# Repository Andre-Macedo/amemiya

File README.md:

# Sistema de Metrologia Lean Tech (Amemiya)

Plataforma integrada de metrologia industrial, gestão de conformidade (ISO/IEC 17025, ILAC-G8, OIML D10, FDA 21 CFR Part 11) e monitoramento contínuo com IoT e inteligência artificial (XGBoost).

---

## 1. Visão Geral da Arquitetura

```mermaid
graph TD
    subgraph Frontend & Clients
        UI["Next.js 16 Frontend (metrology-sass-front)"]
        Admin["Filament 4 Admin Panel (:8000)"]
        Sensors["Sensores Industriais / ESP32 Nodes"]
    end

    subgraph Backend Core (Amemiya)
        Nginx["Nginx (:8000)"]
        App["amemiya-app (PHP 8.3 FPM)"]
        Reverb["Laravel Reverb (:8080 WebSockets)"]
        Worker["Queue Worker (Laravel Queues)"]
        Bridge["MQTT Bridge (iot:mqtt-bridge)"]
    end

    subgraph Data & Messaging
        DB[("MySQL 8.0 (:3307)")]
        Redis[("Redis 7.x (:6379)")]
        MQTT["Mosquitto Broker (:1883)"]
    end

    subgraph Machine Learning
        ML["ML Service (FastAPI / XGBoost :8000)"]
    end

    Sensors -->|MQTT QoS 1| MQTT
    MQTT -->|iot:mqtt-bridge| Bridge
    Bridge --> Redis
    Bridge --> App

    UI -->|REST API| Nginx
    UI -->|WebSockets| Reverb
    Admin --> Nginx
    Nginx --> App

    App --> DB
    App --> Redis
    App --> ML
    Worker --> Redis
    Worker --> DB
    App -->|Broadcast| Reverb
```

---

## 2. Módulos da Aplicação

O sistema é construído sobre uma **arquitetura modular** (`nwidart/laravel-modules`):

- **[`Modules/Metrology/`](Modules/Metrology)**: Motor metrológico completo. Gestão de calibrações, instrumentos, padrões de referência RBC, cálculo de incerteza de medição conforme GUM, bandas de guarda (ILAC-G8), otimização de intervalos (OIML D10), cartas de controle de Shewhart (ILAC-G24), laudos forenses com assinatura digital SHA-256 e trilha encadeada de auditoria imutável (FDA 21 CFR Part 11).
- **[`Modules/IoT/`](Modules/IoT)**: Ingestão de telemetria industrial de vibração e temperatura em tempo real via Mosquitto MQTT, classificação de severidade conforme ISO 20816-3 e integração com modelo preditivo de anomalias.
- **[`Modules/System/`](Modules/System)**: Multi-tenancy central, perfis e matriz de permissões via Filament Shield, auditoria Spatie Activitylog e usuários.
- **[`hardware/`](hardware)**: Projetos completos de eletrônica (KiCad) e mecânica (Autodesk Fusion 360 / STEP) para os nós sensores, gateway LoRa e bancada industrial com proteção NR-12.

---

## 3. Guia Rápido de Instalação (Docker)

### Pré-requisitos
- [Docker Desktop](https://www.docker.com/products/docker-desktop/) (com suporte a Docker Compose v2)
- [Git](https://git-scm.com/)

### Passo a Passo

1. **Clonar o repositório:**
   ```bash
   git clone git@github.com:Andre-Macedo/amemiya.git
   cd amemiya
   ```

2. **Configurar variáveis de ambiente:**
   ```bash
   cp .env.example .env
   ```

3. **Subir os containers:**
   ```bash
   docker compose up -d --build
   ```

4. **Instalar dependências e preparar a aplicação:**
   ```bash
   docker compose exec app composer install
   docker compose exec app php artisan key:generate
   docker compose exec app php artisan migrate
   docker compose exec app php artisan module:migrate Metrology
   docker compose exec app php artisan module:migrate IoT
   docker compose exec app php artisan module:seed Metrology
   docker compose exec app php artisan storage:link
   ```

5. **Criar o usuário administrador do Filament:**
   ```bash
   docker compose exec app php artisan make:filament-user
   ```

---

## 4. Portas e Serviços Locais

| Serviço | Porta Local | Descrição |
| :--- | :--- | :--- |
| **Painel Filament / API** | [http://localhost:8000](http://localhost:8000) | Aplicação web principal |
| **Frontend Next.js** | [http://localhost:3000](http://localhost:3000) | Interface do cliente e monitor IoT |
| **phpMyAdmin** | [http://localhost:8080](http://localhost:8080) | Gerenciador web do MySQL (root/rootpass) |
| **MailHog (SMTP)** | [http://localhost:8025](http://localhost:8025) | Caixa de entrada para e-mails de teste |
| **Mosquitto MQTT** | `localhost:1883` | Broker de mensagens IoT |
| **Redis** | `localhost:6379` | Cache e filas de processamento |
| **MySQL 8.0** | `localhost:3307` | Banco de dados relacional |
| **Laravel Reverb** | `localhost:8080` | Servidor de WebSockets |

---

## 5. Scripts de Qualidade e Testes

Antes de submeter código, execute os scripts de verificação:

```bash
# Executar todos os testes automatizados (Pest)
docker compose exec app composer test

# Verificação de formatação de código (Laravel Pint)
docker compose exec app composer format:test

# Correção automática de formatação
docker compose exec app composer format

# Análise estática de tipos (PHPStan / Larastan)
docker compose exec app composer analyse

# Validação completa de qualidade (Pint + Larastan + Pest)
docker compose exec app composer quality
```

---

## 6. Fluxo de Contribuição e Branches

- **Branch principal de desenvolvimento:** **`develop`**
- **Branch de produção:** **`main`**
- **Todas as Pull Requests devem ter como destino a branch `develop`.**
- Consulte o guia completo em [`CONTRIBUTING.md`](CONTRIBUTING.md) para detalhes sobre Conventional Commits e padrões de arquitetura.

---

## 7. Índice de Documentação Técnica

- **Metrologia e Qualidade:**
  - [`Modules/Metrology/docs/BUSINESS_RULES.md`](Modules/Metrology/docs/BUSINESS_RULES.md) — Manual canônico de regras de negócio, normas ISO e cálculos.
  - [`docs/metrology/METROLOGY_MODULE_GUIDE.md`](docs/metrology/METROLOGY_MODULE_GUIDE.md) — Guia arquitetural completo, diagramas ER e conformidade normativa.
  - [`docs/metrology/USER_ACCEPTANCE_TESTS.md`](docs/metrology/USER_ACCEPTANCE_TESTS.md) — Roteiros de testes de aceitação de usuário (UAT).
- **IoT, Telemetria e MLOps:**
  - [`docs/iot/DECISOES_TECNICAS_E_REFERENCIAS_CIENTIFICAS.md`](docs/iot/DECISOES_TECNICAS_E_REFERENCIAS_CIENTIFICAS.md) — Fundamentação científica e amostragem de vibração.
  - [`docs/iot/REGRAS_DE_NEGOCIO_MLOPS_E_AMOSTRAGEM.md`](docs/iot/REGRAS_DE_NEGOCIO_MLOPS_E_AMOSTRAGEM.md) — Pipeline de machine learning e triagem de anomalias.
  - [`docs/iot/MQTT_SECURITY.md`](docs/iot/MQTT_SECURITY.md) — Diretrizes de segurança, isolamento e ACL do Mosquitto.
  - [`docs/iot/RELATORIO_PCBS.md`](docs/iot/RELATORIO_PCBS.md) — Especificações de eletrônica e esquemáticos.
- **Arquitetura Geral:**
  - [`docs/architecture/TENANCY_ARCHITECTURE.md`](docs/architecture/TENANCY_ARCHITECTURE.md) — Isolamento de dados multi-tenant.
  - [`docs/architecture/WEBSOCKETS_REVERB_GUIDE.md`](docs/architecture/WEBSOCKETS_REVERB_GUIDE.md) — Guia de integração Reverb WebSockets.
  - [`docs/architecture/IMPROVEMENT_PLAN.md`](docs/architecture/IMPROVEMENT_PLAN.md) — Roadmap de melhorias e evolução contínua.

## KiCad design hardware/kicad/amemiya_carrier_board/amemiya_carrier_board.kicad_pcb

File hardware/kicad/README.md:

# Amemiya IoT — Projetos de PCB KiCad (v2.0)

Este repositório contém os projetos de placas de circuito impresso (PCB) desenvolvidos para o sistema de manutenção preditiva e IoT industrial **Amemiya**.

---

## Estrutura dos Projetos KiCad

Os projetos foram modelados de forma **100% modular**, onde os módulos de sensores, microcontrolador e rádio são encaixados na PCB principal através de **soquetes de barra de pinos fêmea (headers 2.54 mm)**, permitindo substituição rápida de qualquer componente sem necessidade de solda direta nos chips.

```
hardware/kicad/
├── amemiya_probe_sensor/            # PCB 1: Sonda de Mancal Ultra-Compacta (25x25 mm)
│   ├── amemiya_probe_sensor.kicad_sch  # Esquemático elétrico KiCad
│   └── amemiya_probe_sensor.kicad_pcb  # Layout da placa PCB
├── amemiya_main_node/               # PCB 2: Nó de Borda Principal ESP32-S3 (70x50 mm)
│   ├── amemiya_main_node.kicad_sch     # Esquemático elétrico KiCad
│   └── amemiya_main_node.kicad_pcb     # Layout da placa PCB
├── amemiya_probe_tower/             # PCB 3: Sonda Cartucho Torre Cilíndrica (24x48 mm)
│   └── amemiya_probe_tower.kicad_pcb   # Layout da placa PCB
├── scripts/                         # Scripts Python de geração procedural e roteamento A*
│   ├── generate_zero_drc_pcbs_v35.py   # Gerador master v35 (PTH, 0 DRC)
│   ├── astar_router_v13.py             # Roteador A* Grid Maze v13
│   └── generate_probe_tower_v5.py      # Gerador da torre v5
└── README.md                         # Este manual
```

---

## 1. PCB 1 — Sonda de Mancal (Probe Sensor Board)

- **Dimensões:** $25.0 \text{ mm} \times 25.0 \text{ mm}$ (formato compacto para mancal de $2.5 \text{ cm}$).
- **Conector de Saída:** Bornes / Pads para cabo blindado 6 vias conectado ao plugue **GX12 6 Pinos**.

### Soquetes de Encaixe dos Sensores na Sonda:

| Ref | Componente / Módulo | Tipo de Soquete | Pinos Utilizados |
|---|---|---|---|
| **J_ACCEL** | Acelerômetro 3D (MPU-6050 / MPU-9250 / ADXL345) | Header Fêmea 1x8 (2.54 mm) | VCC, GND, SCL, SDA |
| **J_MIC** | Microfone Digital I2S (INMP441) | Header Fêmea 1x6 (2.54 mm) | VCC, GND, SD, WS, SCK, L/R (GND) |
| **J_TEMP** | Termômetro (DS18B20 TO-92) | Header Fêmea 1x3 (2.54 mm) | VCC (Pino 3), DATA (Pino 2), GND (Pino 1) |
| **R1** | Resistor Pull-up DS18B20 | Resistor TH / SMD 0805 | $4.7 \text{ k}\Omega$ entre VCC e DATA |
| **C1** | Capacitor Desacoplamento | Capacitor SMD 0805 | $100 \text{ nF}$ entre VCC e GND |

### Mapeamento de Vias do Cabo Único (Conector GX12 6 Vias):

| Pino GX12 | Sinal | Descrição |
|---|---|---|
| **Pino 1** | **VCC (+3.3V)** | Alimentação principal da sonda |
| **Pino 2** | **GND (0V)** | Terra comum |
| **Pino 3** | **I2C_SDA** | Dados I2C do Acelerômetro |
| **Pino 4** | **I2C_SCL** | Clock I2C do Acelerômetro |
| **Pino 5** | **TEMP_DATA** | Sinal 1-Wire do DS18B20 |
| **Pino 6** | **MIC_SD** | Dados I2S do Microfone INMP441 |

---

## 2. PCB 2 — Nó Principal de Borda (Main Edge Node ESP32-S3)

- **Dimensões:** $70.0 \text{ mm} \times 50.0 \text{ mm}$ (Encaixa em caixas herméticas IP65 padrão Patola).
- **Alimentação:** Borne / Conector JST para bateria Lítio 18650 / Módulo BMS TP4056.

### Soquetes de Encaixe dos Módulos na Placa Principal:

| Ref | Componente / Módulo | Tipo de Soquete | Pinos / GPIOs ESP32-S3 |
|---|---|---|---|
| **U_ESP32** | Microcontrolador **ESP32-S3 DevKit** | 2x Headers Fêmea 1x22 (2.54 mm) | Módulo soquetado central |
| **U_LORA** | Módulo Rádio LoRa (E220-900T22D / Ra-02 / SX1276) | Header Fêmea 1x7 ou 1x16 | SPI / UART (TX: GPIO 43, RX: GPIO 44) |
| **U_OLED** | Display OLED 0.96" I2C (128x64) | Header Fêmea 1x4 (2.54 mm) | VCC, GND, SDA (GPIO 8), SCL (GPIO 9) |
| **J_PROBE** | Entrada da Sonda de Mancal | Conector GX12-6 de Painel / Header 1x6 | VCC, GND, SDA (GPIO 8), SCL (GPIO 9), Temp (GPIO 4), MicSD (GPIO 5) |
| **J_TACHO** | Entrada do Tacômetro Hall (KY-003) | Header Fêmea 1x3 (2.54 mm) | VCC, GND, Signal (GPIO 6 com Interrupção) |
| **J_AMP** | Entrada do Alicate Amperométrico (SCT-013) | Jack P2 3.5 mm de Painel | ADC_IN (GPIO 1), GND + Burden Resistor $33\Omega$ |
| **J_SIGNAL**| Saída Sinaleira RGB + Buzzer | Header Macho 1x5 (2.54 mm) | VCC, Red (GPIO 10), Green (GPIO 11), Blue (GPIO 12), Buzzer (GPIO 13) |
| **J_BAT** | Entrada da Bateria 3.7V / TP4056 | Conector JST-PH 2 Pinos | VCC_BAT, GND |

---

## 3. Instruções para Abertura no KiCad

1. Instale o **KiCad 7.0 ou 8.0** ([kicad.org](https://www.kicad.org/)).
2. Abra o KiCad e navegue até a pasta `hardware/kicad/amemiya_probe_sensor/` ou `hardware/kicad/amemiya_main_node/`.
3. Dê um duplo clique no arquivo `.kicad_sch` para abrir o editor de esquemáticos (**Eeschema**) ou no arquivo `.kicad_pcb` para abrir o layout de placa (**Pcbnew**).
4. Para gerar arquivos de fabricação (Gerber e NC Drill):
   - No Pcbnew, vá em **Arquivo $\rightarrow$ Plotter (Geração de Gerber)**.
   - Selecione a camada superior (`F.Cu`), inferior (`B.Cu`), máscara de solda (`F.Mask`, `B.Mask`), serigrafia (`F.Silkscreen`) e borda da placa (`Edge.Cuts`).
   - Clique em **Plotar** e depois em **Gerar Arquivos de Perfuração (Drill Files)**.

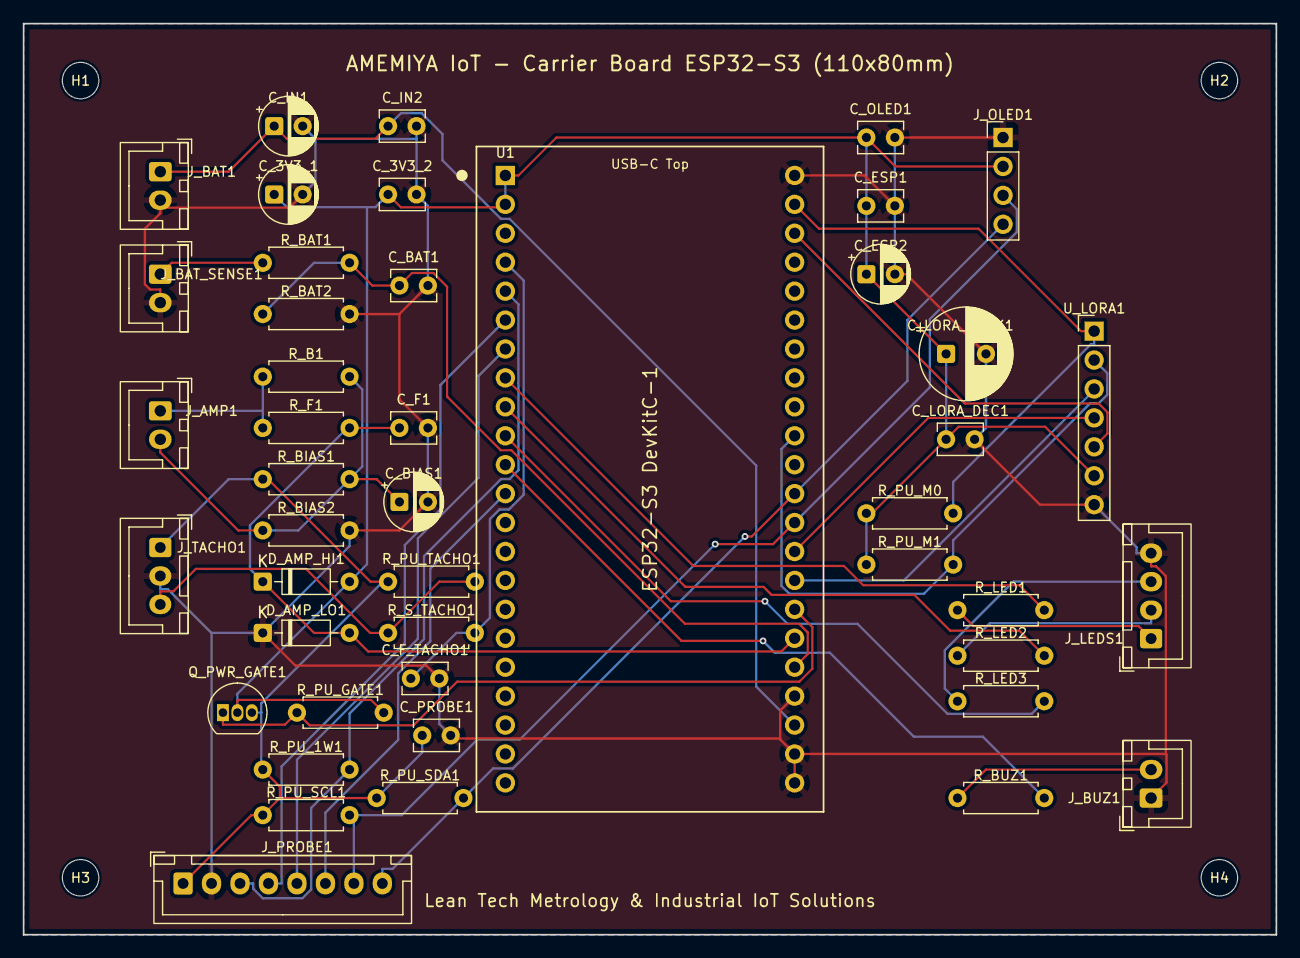
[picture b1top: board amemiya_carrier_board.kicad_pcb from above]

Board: 2 copper layers, 110.0 x 80.0 mm, 49 parts (0 on the bottom side), 31 nets.

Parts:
C_3V3_1: 10uF; CP_Radial_D5.0mm_P2.50mm
C_3V3_2: 100nF; C_Disc_D3.8mm_W2.6mm_P2.50mm
C_BAT1: 100nF; C_Disc_D3.8mm_W2.6mm_P2.50mm
C_BIAS1: 10uF; CP_Radial_D5.0mm_P2.50mm
C_ESP1: 100nF; C_Disc_D3.8mm_W2.6mm_P2.50mm
C_ESP2: 10uF; CP_Radial_D5.0mm_P2.50mm
C_F1: 10nF; C_Disc_D3.8mm_W2.6mm_P2.50mm
C_F_TACHO1: 100pF; C_Disc_D3.8mm_W2.6mm_P2.50mm
C_IN1: 10uF; CP_Radial_D5.0mm_P2.50mm
C_IN2: 100nF; C_Disc_D3.8mm_W2.6mm_P2.50mm
C_LORA_BULK1: 470uF 16V; CP_Radial_D8.0mm_P3.50mm
C_LORA_DEC1: 100nF; C_Disc_D3.8mm_W2.6mm_P2.50mm
C_OLED1: 100nF; C_Disc_D3.8mm_W2.6mm_P2.50mm
C_PROBE1: 100nF; C_Disc_D3.8mm_W2.6mm_P2.50mm
D_AMP_HI1: BAT42; D_DO-35_SOD27_P7.62mm_Horizontal
D_AMP_LO1: BAT42; D_DO-35_SOD27_P7.62mm_Horizontal
H1, H2, H3, H4: M3; MountingHole_3.2mm_M3
J_AMP1: Clamp_SCT013_2P; JST_XH_B2B-XH-A_1x02_P2.50mm_Vertical
J_BAT1: Bateria_BMS_2P; JST_XH_B2B-XH-A_1x02_P2.50mm_Vertical
J_BAT_SENSE1: Sense_VBAT_2P; JST_XH_B2B-XH-A_1x02_P2.50mm_Vertical
J_BUZ1: Buzzer_2P; JST_XH_B2B-XH-A_1x02_P2.50mm_Vertical
J_LEDS1: Status_LEDs_4P; JST_XH_B4B-XH-A_1x04_P2.50mm_Vertical
J_OLED1: Display_OLED_4P; PinHeader_1x04_P2.54mm_Vertical
J_PROBE1: Sonda_Torre_GX16_8P; JST_XH_B8B-XH-A_1x08_P2.50mm_Vertical
J_TACHO1: Tacometro_3P; JST_XH_B3B-XH-A_1x03_P2.50mm_Vertical
Q_PWR_GATE1: AO3401A (TO-92); TO-92_Inline
R_B1: 33R; R_Axial_DIN0207_L6.3mm_D2.5mm_P7.62mm_Horizontal
R_BAT1, R_BAT2: 100k 1%; R_Axial_DIN0207_L6.3mm_D2.5mm_P7.62mm_Horizontal
R_BIAS1, R_BIAS2: 100k 1%; R_Axial_DIN0207_L6.3mm_D2.5mm_P7.62mm_Horizontal
R_BUZ1: 100R; R_Axial_DIN0207_L6.3mm_D2.5mm_P7.62mm_Horizontal
R_F1: 1k; R_Axial_DIN0207_L6.3mm_D2.5mm_P7.62mm_Horizontal
R_LED1, R_LED2, R_LED3: 330R; R_Axial_DIN0207_L6.3mm_D2.5mm_P7.62mm_Horizontal
R_PU_1W1: 4.7k; R_Axial_DIN0207_L6.3mm_D2.5mm_P7.62mm_Horizontal
R_PU_GATE1: 100k; R_Axial_DIN0207_L6.3mm_D2.5mm_P7.62mm_Horizontal
R_PU_M0, R_PU_M1: 10k; R_Axial_DIN0207_L6.3mm_D2.5mm_P7.62mm_Horizontal
R_PU_SCL1: 4.7k; R_Axial_DIN0207_L6.3mm_D2.5mm_P7.62mm_Horizontal
R_PU_SDA1: 4.7k; R_Axial_DIN0207_L6.3mm_D2.5mm_P7.62mm_Horizontal
R_PU_TACHO1: 4.7k; R_Axial_DIN0207_L6.3mm_D2.5mm_P7.62mm_Horizontal
R_S_TACHO1: 1k; R_Axial_DIN0207_L6.3mm_D2.5mm_P7.62mm_Horizontal
U1: ESP32-S3-DevKitC-1
U_LORA1: E32-TTL-100; PinHeader_1x07_P2.54mm_Vertical

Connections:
+3V3: C_3V3_1.1, C_3V3_2.1, C_ESP1.1, C_ESP2.1, C_LORA_BULK1.1, C_LORA_DEC1.1, C_OLED1.1, D_AMP_HI1.2, J_OLED1.2, Q_PWR_GATE1.2, R_PU_GATE1.2, R_PU_M0.1, R_PU_M1.1, U1.1 (3V3), U1.2 (3V3), U_LORA1.6
+5V: C_IN1.1, C_IN2.1, J_BAT1.1, U1.42 (5V_(VBUS))
/MCU_ESP32S3/1W_DQ: J_PROBE1.3, R_PU_1W1.2, U1.5 (GPIO5_(1W_DQ))
/MCU_ESP32S3/AMP_ADC: C_F1.1, D_AMP_HI1.1, D_AMP_LO1.2, R_F1.2, U1.39 (GPIO2_(AMP_ADC))
/MCU_ESP32S3/GPIO_BUZZER: R_BUZ1.2, U1.11 (GPIO18_(BUZZER))
/MCU_ESP32S3/GPIO_LED_BLU: R_LED3.2, U1.10 (GPIO17_(LED_BLU))
/MCU_ESP32S3/GPIO_LED_GRN: R_LED1.2, U1.8 (GPIO15_(LED_GRN))
/MCU_ESP32S3/GPIO_LED_ORG: R_LED2.2, U1.9 (GPIO16_(LED_ORG))
/MCU_ESP32S3/I2C_SCL: J_OLED1.3, J_PROBE1.7, R_PU_SCL1.2, U1.35 (GPIO42_(I2C_SCL))
/MCU_ESP32S3/I2C_SDA: J_OLED1.4, J_PROBE1.8, R_PU_SDA1.2, U1.34 (GPIO41_(I2C_SDA))
/MCU_ESP32S3/I2S_SCK: J_PROBE1.5, U1.7 (GPIO7_(I2S_SCK))
/MCU_ESP32S3/I2S_SD: J_PROBE1.4, U1.6 (GPIO6_(I2S_SD))
/MCU_ESP32S3/I2S_WS: J_PROBE1.6, U1.12 (GPIO8_(I2S_WS))
/MCU_ESP32S3/LORA_AUX: U1.25 (GPIO47_(LORA_AUX)), U_LORA1.5
/MCU_ESP32S3/LORA_M0: R_PU_M0.2, U1.24 (GPIO38_(LORA_M0)), U_LORA1.1
/MCU_ESP32S3/LORA_M1: R_PU_M1.2, U1.32 (GPIO39_(LORA_M1)), U_LORA1.2
/MCU_ESP32S3/LORA_RX: U1.36 (GPIO44_(LORA_RX)), U_LORA1.4
/MCU_ESP32S3/LORA_TX: U1.37 (GPIO43_(LORA_TX)), U_LORA1.3
/MCU_ESP32S3/PWR_GATE_EN: Q_PWR_GATE1.1, R_PU_GATE1.1, U1.38 (GPIO21_(PWR_GATE))
/MCU_ESP32S3/TACHO: C_F_TACHO1.1, R_S_TACHO1.2, U1.4 (GPIO4_(TACHO))
/MCU_ESP32S3/VBAT_ADC: C_BAT1.1, R_BAT1.2, R_BAT2.1, U1.40 (GPIO1_(VBAT_ADC))
/Power_Supply/VBAT_RAW: J_BAT_SENSE1.1, R_BAT1.1
/Sensors_AFE/+3V3_SWITCHED: C_PROBE1.1, J_PROBE1.1, J_TACHO1.1, Q_PWR_GATE1.3, R_BIAS1.1, R_PU_1W1.1, R_PU_SCL1.1, R_PU_SDA1.1, R_PU_TACHO1.1
/Sensors_AFE/TACHO_RAW: J_TACHO1.3, R_PU_TACHO1.2, R_S_TACHO1.1
GND: C_3V3_1.2, C_3V3_2.2, C_BAT1.2, C_BIAS1.2, C_ESP1.2, C_ESP2.2, C_F1.2, C_F_TACHO1.2, C_IN1.2, C_IN2.2, C_LORA_BULK1.2, C_LORA_DEC1.2, C_OLED1.2, C_PROBE1.2, D_AMP_LO1.1, J_BAT1.2, J_BAT_SENSE1.2, J_BUZ1.1, J_LEDS1.4, J_OLED1.1, J_PROBE1.2, J_TACHO1.2, R_BAT2.2, R_BIAS2.2, U1.23 (GND), U1.41 (GND), U1.43 (GND), U1.44 (GND), U_LORA1.7
unnamed: J_AMP1.1, R_B1.1, R_F1.1
unnamed: C_BIAS1.1, J_AMP1.2, R_B1.2, R_BIAS1.2, R_BIAS2.1
unnamed: J_BUZ1.2, R_BUZ1.1
unnamed: J_LEDS1.1, R_LED1.1
unnamed: J_LEDS1.2, R_LED2.1
unnamed: J_LEDS1.3, R_LED3.1

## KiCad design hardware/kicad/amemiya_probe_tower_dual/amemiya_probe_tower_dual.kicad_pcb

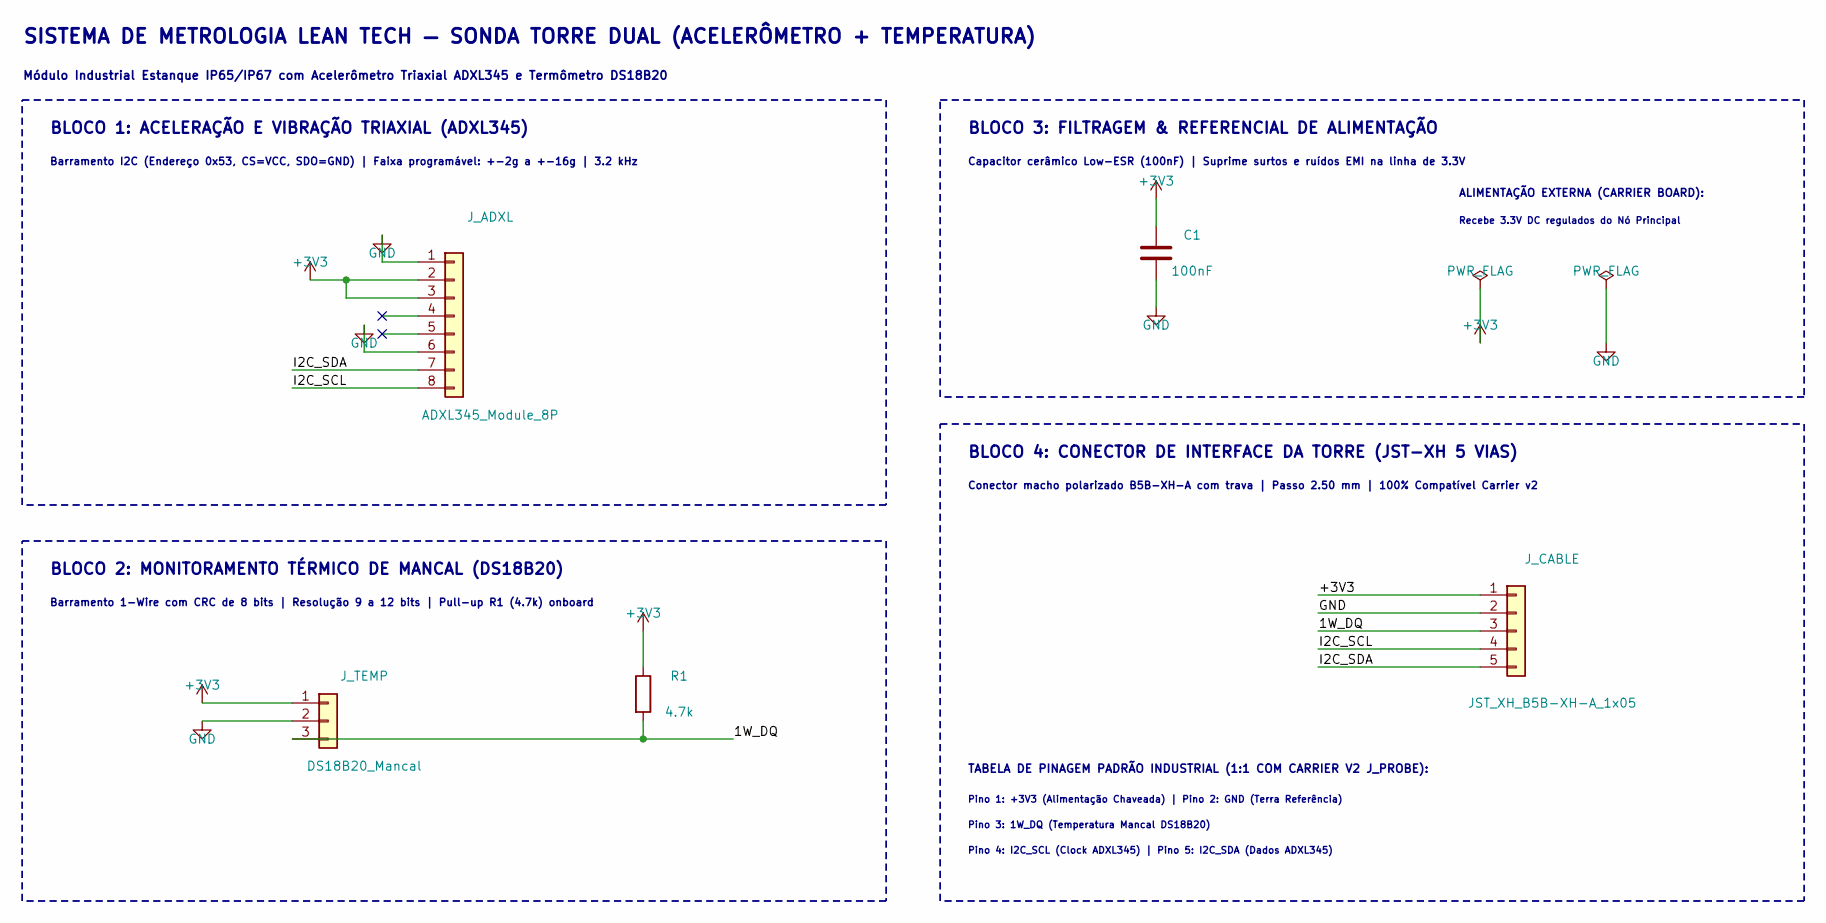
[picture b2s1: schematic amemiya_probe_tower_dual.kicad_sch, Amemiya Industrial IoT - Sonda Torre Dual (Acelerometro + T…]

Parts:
C1: 100nF; C_Disc_D3.8mm_W2.6mm_P2.50mm
J_ADXL: ADXL345_Module_8P; PinHeader_1x08_P2.54mm_Vertical
J_CABLE: JST_XH_B5B-XH-A_1x05; JST_XH_B5B-XH-A_1x05_P2.50mm_Vertical
J_TEMP: DS18B20_Mancal; PinHeader_1x03_P2.54mm_Vertical
R1: 4.7k; R_Axial_DIN0204_L3.6mm_D1.6mm_P5.08mm_Horizontal

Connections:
+3V3: C1.1, J_ADXL.2, J_ADXL.3, J_CABLE.1, J_TEMP.1, R1.1
/1W_DQ: J_CABLE.3, J_TEMP.3, R1.2
/I2C_SCL: J_ADXL.8, J_CABLE.4
/I2C_SDA: J_ADXL.7, J_CABLE.5
GND: C1.2, J_ADXL.1, J_ADXL.6, J_CABLE.2, J_TEMP.2

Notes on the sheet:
SISTEMA DE METROLOGIA LEAN TECH — SONDA TORRE DUAL (ACELERÔMETRO + TEMPERATURA)
Módulo Industrial Estanque IP65/IP67 com Acelerômetro Triaxial ADXL345 e Termômetro DS18B20
BLOCO 1: ACELERAÇÃO E VIBRAÇÃO TRIAXIAL (ADXL345)
Barramento I2C (Endereço 0x53, CS=VCC, SDO=GND) | Faixa programável: +-2g a +-16g | 3.2 kHz
BLOCO 2: MONITORAMENTO TÉRMICO DE MANCAL (DS18B20)
Barramento 1-Wire com CRC de 8 bits | Resolução 9 a 12 bits | Pull-up R1 (4.7k) onboard
BLOCO 3: FILTRAGEM & REFERENCIAL DE ALIMENTAÇÃO
Capacitor cerâmico Low-ESR (100nF) | Suprime surtos e ruídos EMI na linha de 3.3V
ALIMENTAÇÃO EXTERNA (CARRIER BOARD):
Recebe 3.3V DC regulados do Nó Principal
BLOCO 4: CONECTOR DE INTERFACE DA TORRE (JST-XH 5 VIAS)
Conector macho polarizado B5B-XH-A com trava | Passo 2.50 mm | 100% Compatível Carrier v2
TABELA DE PINAGEM PADRÃO INDUSTRIAL (1:1 COM CARRIER V2 J_PROBE):
Pino 1: +3V3 (Alimentação Chaveada) | Pino 2: GND (Terra Referência)
Pino 3: 1W_DQ (Temperatura Mancal DS18B20)
Pino 4: I2C_SCL (Clock ADXL345) | Pino 5: I2C_SDA (Dados ADXL345)

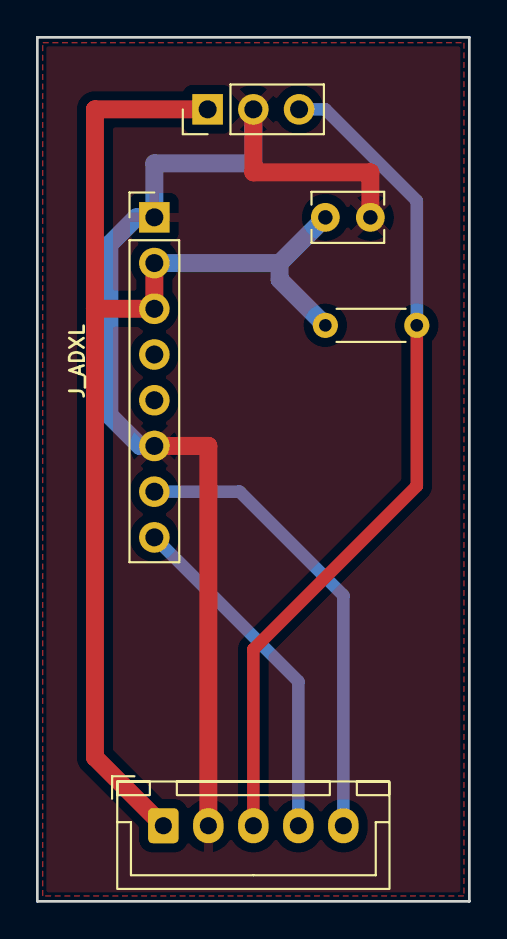
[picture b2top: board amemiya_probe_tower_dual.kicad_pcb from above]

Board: 2 copper layers, 24.0 x 48.0 mm, 5 parts (0 on the bottom side), 5 nets.

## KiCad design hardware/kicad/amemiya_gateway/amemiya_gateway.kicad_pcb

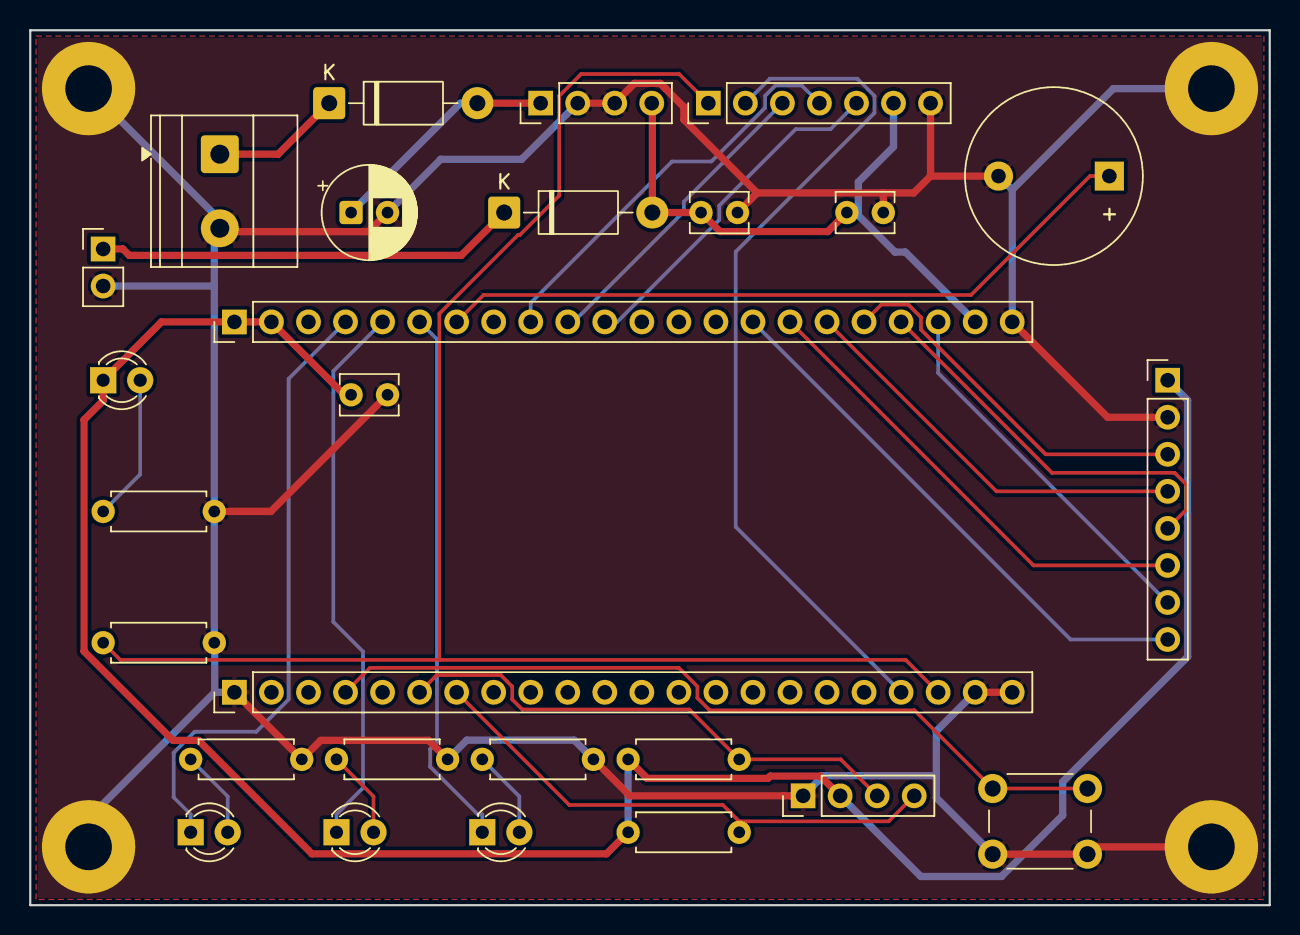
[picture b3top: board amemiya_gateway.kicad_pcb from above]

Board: 2 copper layers, 85.0 x 60.0 mm, 31 parts (0 on the bottom side), 28 nets.

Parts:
BZ1: Buzzer_5V; Buzzer_12x9.5RM7.6
C1: 470uF_25V; CP_Radial_D6.3mm_P2.50mm
C2, C3, C4: 100nF; C_Disc_D3.8mm_W2.6mm_P2.50mm
D1, D2: 1N5819; D_DO-41_SOD81_P10.16mm_Horizontal
D_LORA: Azul_3mm; LED_D3.0mm
D_MQTT: Amarelo_3mm; LED_D3.0mm
D_NET: Verde_3mm; LED_D3.0mm
D_PWR: LED_PWR_Verde; LED_D3.0mm
H1, H2, H3, H4: MountingHole_M3; MountingHole_3.2mm_M3_Pad
J_ETH: W5500_Ethernet; PinHeader_1x08_P2.54mm_Vertical
J_OLED: OLED_SSD1306; PinHeader_1x04_P2.54mm_Vertical
J_PWR_IN: TerminalBlock_9-24V; TerminalBlock_Phoenix_MKDS-1,5-2-5.08_1x02_P5.08mm_Horizont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
J_USB_PWR: Conn_USB_5V_AUX; PinHeader_1x02_P2.54mm_Vertical
R_LORA: 330; R_Axial_DIN0207_L6.3mm_D2.5mm_P7.62mm_Horizontal
R_M0: 10k; R_Axial_DIN0207_L6.3mm_D2.5mm_P7.62mm_Horizontal
R_MQTT: 330; R_Axial_DIN0207_L6.3mm_D2.5mm_P7.62mm_Horizontal
R_NET: 330; R_Axial_DIN0207_L6.3mm_D2.5mm_P7.62mm_Horizontal
R_PWR: 1k; R_Axial_DIN0207_L6.3mm_D2.5mm_P7.62mm_Horizontal
R_SCL: 4.7k; R_Axial_DIN0207_L6.3mm_D2.5mm_P7.62mm_Horizontal
R_SDA: 4.7k; R_Axial_DIN0207_L6.3mm_D2.5mm_P7.62mm_Horizontal
SW_CFG: Botao_Config; SW_PUSH_6mm_H5mm
U_BUCK: MP1584EN_Buck; PinHeader_1x04_P2.54mm_Vertical
U_ESP_L: ESP32-S3_Left; PinHeader_1x22_P2.54mm_Vertical
U_ESP_R: ESP32-S3_Right; PinHeader_1x22_P2.54mm_Vertical
U_LORA: E220-900T22D; PinHeader_1x07_P2.54mm_Vertical

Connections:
+3V3: C3.1, D_PWR.1, J_ETH.1, J_OLED.2, R_SCL.1, R_SDA.1, U_ESP_L.1, U_ESP_L.2
+5V: C2.1, C4.1, D2.2, U_BUCK.4, U_ESP_L.21, U_LORA.6
/BTN_CONFIG: SW_CFG.1, U_ESP_R.4
/BUZZER: BZ1.1, U_ESP_L.7
/ETH_CS: J_ETH.6, U_ESP_L.16
/ETH_INT: J_ETH.7, U_ESP_L.20
/ETH_MISO: J_ETH.5, U_ESP_L.19
/ETH_MOSI: J_ETH.4, U_ESP_L.17
/ETH_RST: J_ETH.8, U_ESP_L.15
/ETH_SCK: J_ETH.3, U_ESP_L.18
/I2C_SCL: J_OLED.3, R_SCL.2, U_ESP_R.6
/I2C_SDA: J_OLED.4, R_SDA.2, U_ESP_R.7
/LED_LORA_RX: D_LORA.1, U_ESP_L.4
/LED_MQTT_OK: D_MQTT.1, U_ESP_L.5
/LED_NET_ACT: D_NET.1, U_ESP_L.6
/LORA_AUX: U_ESP_L.11, U_LORA.5
/LORA_M0: R_M0.1, U_ESP_R.20, U_LORA.1
/LORA_M1: U_ESP_R.19, U_LORA.2
/LORA_RX: U_ESP_L.9, U_LORA.4
/LORA_TX: U_ESP_L.10, U_LORA.3
GND: BZ1.2, C1.2, C2.2, C3.2, C4.2, H1.1, H2.1, H3.1, H4.1, J_ETH.2, J_OLED.1, J_PWR_IN.2, J_USB_PWR.2, R_LORA.2, R_M0.2, R_MQTT.2, R_NET.2, R_PWR.2, SW_CFG.2, U_BUCK.2, U_BUCK.3, U_ESP_L.22, U_ESP_R.1, U_ESP_R.21, U_ESP_R.22, U_LORA.7
unnamed: C1.1, D1.2, U_BUCK.1
unnamed: D1.1, J_PWR_IN.1
unnamed: D2.1, J_USB_PWR.1
unnamed: D_LORA.2, R_LORA.1
unnamed: D_MQTT.2, R_MQTT.1
unnamed: D_NET.2, R_NET.1
unnamed: D_PWR.2, R_PWR.1

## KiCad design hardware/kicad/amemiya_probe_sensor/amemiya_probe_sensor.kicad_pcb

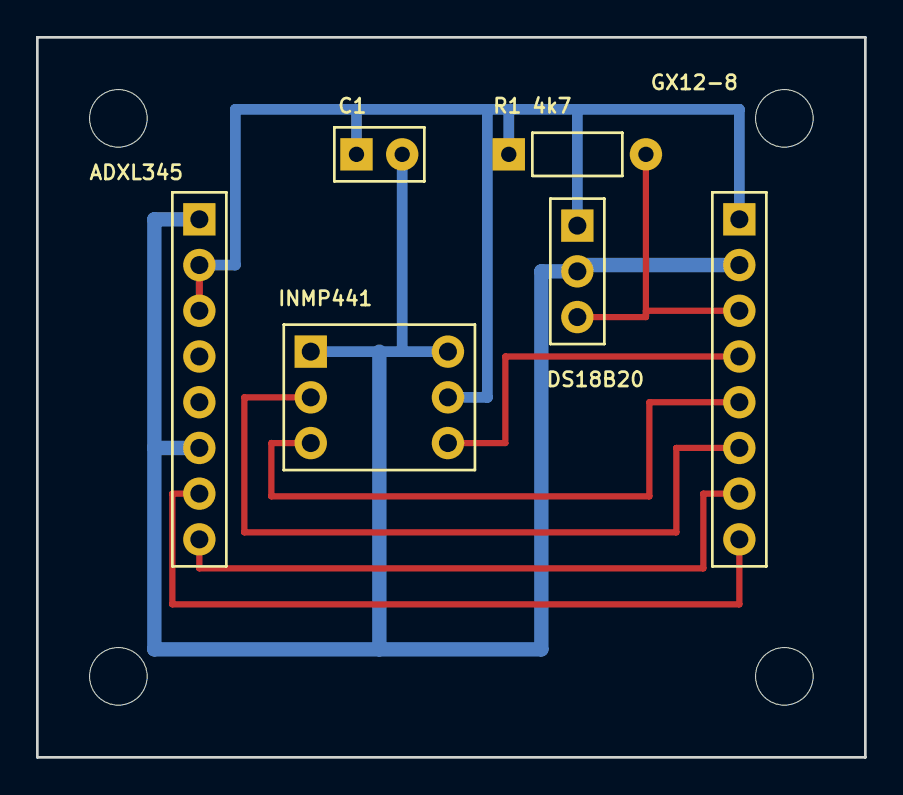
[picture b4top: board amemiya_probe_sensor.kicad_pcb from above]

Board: 2 copper layers, 46.0 x 40.0 mm, 10 parts (0 on the bottom side), 8 nets.

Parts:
C1: (no value)
H: (no value)
H#2, H#3, H#4: (no value)
J_ADXL: (no value)
J_CABLE: (no value)
J_MIC: (no value)
J_TEMP: (no value)
R1: (no value)

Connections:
1W_DQ: J_CABLE.3, J_TEMP.3, R1.2
+3V3: C1.1, J_ADXL.2, J_ADXL.3, J_CABLE.1, J_MIC.5, J_TEMP.1, R1.1
GND: C1.2, J_ADXL.1, J_ADXL.6, J_CABLE.2, J_MIC.1, J_MIC.4, J_TEMP.2
I2C_SCL: J_ADXL.8, J_CABLE.7
I2C_SDA: J_ADXL.7, J_CABLE.8
I2S_SCK: J_CABLE.5, J_MIC.3
I2S_SD: J_CABLE.4, J_MIC.6
I2S_WS: J_CABLE.6, J_MIC.2

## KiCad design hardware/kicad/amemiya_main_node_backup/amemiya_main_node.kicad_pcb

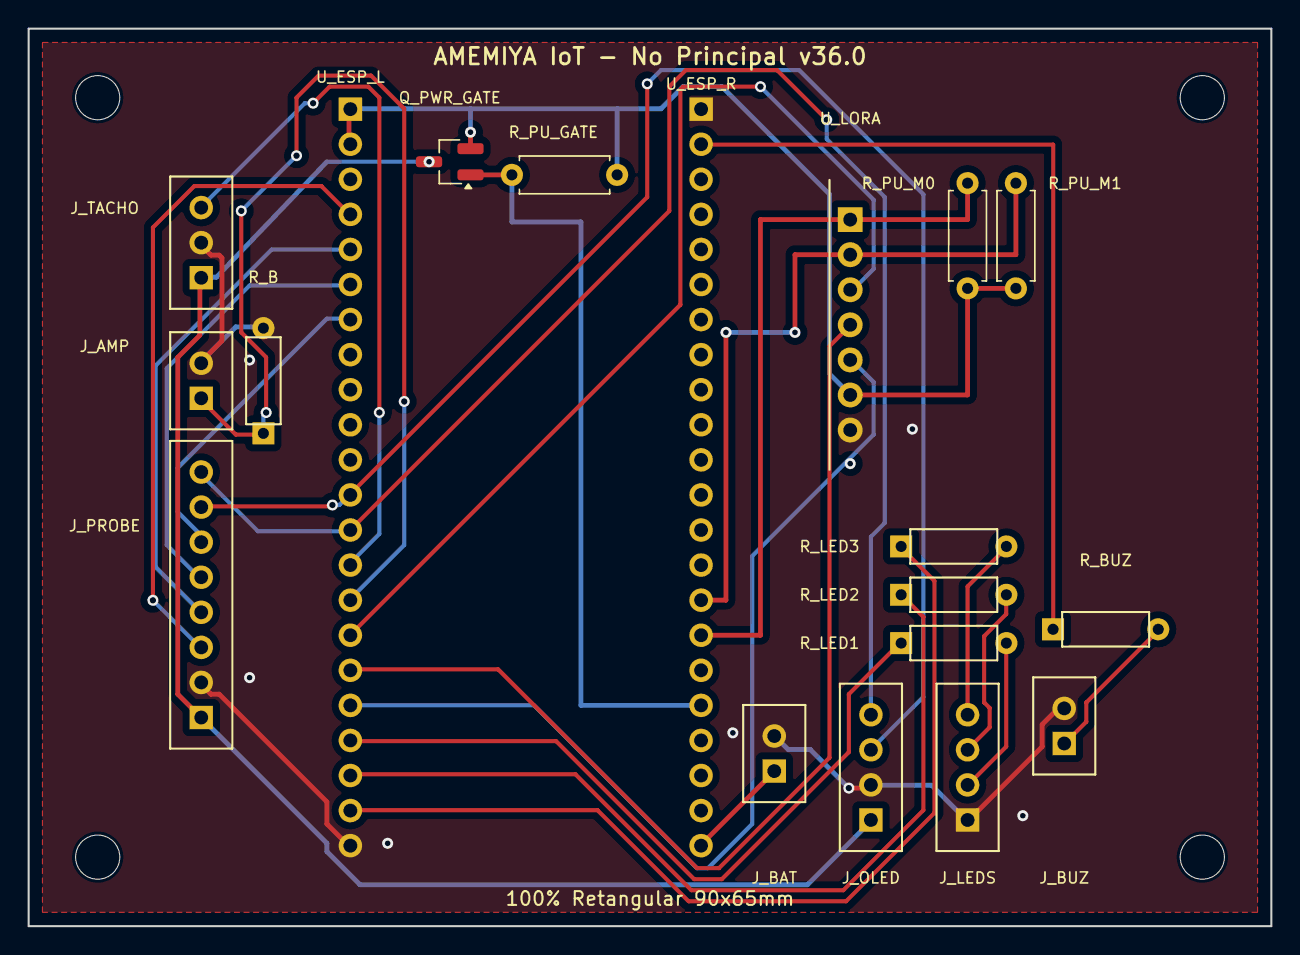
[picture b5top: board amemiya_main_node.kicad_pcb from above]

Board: 2 copper layers, 90.0 x 65.0 mm, 23 parts (0 on the bottom side), 26 nets.

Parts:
H: M3; MountingHole_3.2mm_M3
H#2, H#3, H#4: M3; MountingHole_3.2mm_M3
J_AMP: Clamp_SCT013_2P; JST_XH_B2B-XH-A_1x02_P2.54mm_Vertical
J_BAT: Bateria_BMS_2P; JST_XH_B2B-XH-A_1x02_P2.54mm_Vertical
J_BUZ: Buzzer_2P; JST_XH_B2B-XH-A_1x02_P2.54mm_Vertical
J_LEDS: Status_LEDs_4P; JST_XH_B4B-XH-A_1x04_P2.54mm_Vertical
J_OLED: Display_OLED_4P; JST_XH_B4B-XH-A_1x04_P2.54mm_Vertical
J_PROBE: Sonda_Torre_GX12_8P; JST_XH_B8B-XH-A_1x08_P2.54mm_Vertical
J_TACHO: Tacometro_3P; JST_XH_B3B-XH-A_1x03_P2.54mm_Vertical
Q_PWR_GATE: AO3401A; SOT-23_Handsoldering
R_B: 33R; R_Axial_DIN0207_L6.3mm_D2.5mm_P7.62mm_Horizontal
R_BUZ: 100R; R_Axial_DIN0207_L6.3mm_D2.5mm_P7.62mm_Horizontal
R_LED1, R_LED2, R_LED3: 330R; R_Axial_DIN0207_L6.3mm_D2.5mm_P7.62mm_Horizontal
R_PU_GATE: 100k; R_Axial_DIN0207_L6.3mm_D2.5mm_P7.62mm_Horizontal
R_PU_M0, R_PU_M1: 10k; R_Axial_DIN0207_L6.3mm_D2.5mm_P7.62mm_Horizontal
U_ESP_L: ESP32-S3_Header_1x22; PinHeader_1x22_P2.54mm_Vertical
U_ESP_R: ESP32-S3_Header_1x22; PinHeader_1x22_P2.54mm_Vertical
U_LORA: E32-TTL-100; Ebyte_E32-TTL-100_SIP7

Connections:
1W_DQ: J_PROBE.3, U_ESP_L.4
+3V3: Q_PWR_GATE.2, R_PU_GATE.2, R_PU_M0.2, R_PU_M1.2, U_ESP_L.1, U_ESP_L.2, U_LORA.6
+3V3_SWITCHED: J_OLED.1, J_PROBE.1, J_TACHO.1, Q_PWR_GATE.3
AMP_ADC: J_AMP.1, R_B.1, U_ESP_L.15
BUZZER_OUT: J_BUZ.1, R_BUZ.2
GND: J_AMP.2, J_BAT.2, J_BUZ.2, J_LEDS.1, J_OLED.2, J_PROBE.2, J_TACHO.2, R_B.2, U_ESP_L.22, U_ESP_R.1, U_LORA.7
GPIO_BUZZER: R_BUZ.1, U_ESP_R.2
GPIO_LED_BLU: R_LED3.1, U_ESP_L.21
GPIO_LED_GRN: R_LED1.1, U_ESP_L.19
GPIO_LED_ORG: R_LED2.1, U_ESP_L.20
I2C_SCL: J_OLED.3, J_PROBE.7, U_ESP_L.12
I2C_SDA: J_OLED.4, J_PROBE.8, U_ESP_L.13
I2S_SCK: J_PROBE.5, U_ESP_L.6
I2S_SD: J_PROBE.4, U_ESP_L.5
I2S_WS: J_PROBE.6, U_ESP_L.7
LED_BLU: J_LEDS.4, R_LED3.2
LED_GRN: J_LEDS.2, R_LED1.2
LED_ORG: J_LEDS.3, R_LED2.2
LORA_AUX: U_ESP_L.18, U_LORA.5
LORA_M0: R_PU_M0.1, U_ESP_R.16, U_LORA.1
LORA_M1: R_PU_M1.1, U_ESP_R.15, U_LORA.2
LORA_RX: U_ESP_L.17, U_LORA.4
LORA_TX: U_ESP_L.16, U_LORA.3
PWR_GATE_EN: Q_PWR_GATE.1, R_PU_GATE.1, U_ESP_R.18
TACHO: J_TACHO.3, U_ESP_L.14
VBAT: J_BAT.1, U_ESP_R.22

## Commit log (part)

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2025-09-09 chore: inicializar projeto Laravel com configuracoes Docker, Nginx e PHP
2025-09-18 add metrology module
2025-09-18 feat(metrologia): criar estrutura inicial do modulo Metrology no Laravel
2025-09-29 feat - implement stations, accessLog, checklists
2025-09-29 feat(metrologia): implementar estacoes de trabalho, logs de acesso e checklists metrologicos
2025-10-04 feat - improves checklists
2025-10-04 feat(metrologia): adicionar itens de modelo de checklist e tabela de checklist_items
2025-10-06 feat(metrologia): aprimorar recursos de checklist e fluxos de criacao de calibracao
2025-10-08 feat - add labels
2025-10-08 feat(metrologia): adicionar rotulos e configuracoes de navegacao no Filament
2025-10-12 feat: fix dockerfile and docker-compose.yml
2025-10-12 fix(docker): ajustar configuracoes de build no Dockerfile e docker-compose.yml
2025-10-12 feat(api): implementar endpoints de api para instrumentos, calibracoes e logs de acesso com Sanctum
2025-10-12 feat: add api
2025-10-13 feat(metrologia): adicionar tipos de instrumentos, factories, steps e historico de calibracoes
2025-10-13 feat - add types and factories, changes seeder, add steps and history.
2025-10-13 feat: edits seeder and ChecklistTemplateInfolist.php
2025-10-13 feat(metrologia): atualizar seeder de metrologia e infolist de modelos de checklist
2025-10-13 feat: add migration
2025-10-13 feat(metrologia): criar migration para campos adicionais de itens de checklist
2025-10-14 feat(metrologia): refatorar formularios e tabelas de modelos de checklist no Filament
2025-10-14 feat - changes ChecklistTemplate.php
2025-10-14 feat - changes refernce type ChecklistItem.php
2025-10-14 feat(metrologia): vincular tipos de referencia aos itens de checklist na calibracao
2025-10-15 feat - ajustes e adiciona tipo de bloco de referencia.
2025-10-15 feat(metrologia): adicionar tipos de blocos padrao de referencia e formularios de calibracao
2025-10-16 feat - add filament shield
2025-10-16 feat(seguranca): integrar Filament Shield com controle de perfis e permissoes
2025-10-18 feat - bunch of changes
2025-10-18 refactor(metrologia): aprimorar telas e recursos de logs de acesso e calibracoes no Filament
2025-10-20 feat(metrologia): otimizar listagem de instrumentos com widget de estatisticas metrologicas
2025-10-20 feat - improve list instruments screen
2025-10-20 fix(database): ajustar chaves estrangeiras e integridade referencial nas calibracoes
2025-10-20 feat: add fks properly
2025-10-22 refactor(metrologia): reestruturar modelos e formularios de calibracoes e padroes de referencia
2025-10-22 feat: refactor calibrations and reference standards
2025-10-22 refactor(metrologia): refinar validacoes no formulario CalibrationForm
2025-10-22 feat - adjust CalibrationForm.php
2025-10-22 feat - adjust refactor
2025-10-22 refactor(metrologia): padronizar infolist e tabelas de calibracoes no Filament
2025-10-25 feat - add system Cluster
2025-10-25 feat(sistema): organizar painel administrativo com clusters e atualizar documentacao
2025-10-26 feat: fix CalibrationInfolist.php
2025-10-26 fix(metrologia): corrigir exibicao de campos no infolist de calibracao
2025-10-29 ci(github): configurar pipeline de integracao e deploy continuo no GitHub Actions
2025-10-29 feat: add ci/cd
2025-10-29 feat: add ci/cd 2
2025-10-29 ci(github): ajustar etapas de cache e dependencias no workflow de deploy
2025-10-29 ci(github): remover configuracao desnecessaria no pipeline de deploy
2025-10-29 feat: add ci/cd 3
2025-10-29 feat: add ci/cd 4
2025-10-29 ci(github): aprimorar passos de deploy e migracao remota no GitHub Actions
2025-10-29 ci(github): ajustar parametros de conexao ssh no deploy de producao
2025-10-31 feat - ajustes CalibrationForm.php
2025-10-31 refactor(metrologia): sincronizar campos de calibracao com schemas de instrumentos
2025-11-12 feat - ajustes docker
2025-11-12 chore(docker): otimizar opcache.ini e configuracoes de build do Docker
2025-11-19 refactor(sistema): padronizar serializacao de instrumentos na API e dados de usuario
2025-11-19 feat - ajustes layout
2025-11-19 style(front): personalizar tema Tailwind do painel administrativo Filament
2025-11-19 feat - ajustes layout 2
2025-11-29 feat(metrologia): implementar comando de verificacao de status de instrumentos e regras metrologicas
2025-11-29 feat - novas implementações
2025-11-30 Adiciona configurações de produção (.prod)
2025-11-30 feat(deploy): adicionar configuracoes de ambiente de producao (.prod) com Nginx e Docker Compose
2025-11-30 feat - ajuste badges
2025-11-30 style(metrologia): ajustar badges de status no resource de instrumentos e widgets
2025-12-02 feat - add apo
2025-12-02 feat(api): disponibilizar endpoints de dashboard metrologico e calibracoes
2025-12-02 feat(api): registrar rotas de consulta rapida de calibracao na API
2025-12-02 feat(api): adicionar alias de rota para consulta de calibracoes
2025-12-05 feat - changes apo
2025-12-05 feat(api): expandir controlador de calibracoes com filtros e paginacao
2025-12-05 fix(api): ajustar tipagem de resposta no controlador de calibracoes
2025-12-05 refactor(api): otimizar tratamento de excecoes e formato json do controlador de calibracoes
2025-12-05 feat(api): incluir campos metrologicos detalhados no retorno de calibracoes
2025-12-06 fix(api): corrigir parametro de busca de instrumentos na API
2025-12-06 feat - changes api 3
2025-12-06 feat - changes api 4
2025-12-06 feat(api): incluir dados de incerteza e criterios de aceitacao no payload de calibracoes
2025-12-06 refactor(api): padronizar validacoes de entrada no controlador de calibracoes
2025-12-06 feat - changes api 5
2025-12-06 feat - changes api 6
2025-12-06 fix(api): ajustar resolucao de status de calibracao na API
2025-12-06 feat(metrologia): aprimorar modelo e formulario de padroes de referencia
2025-12-06 feat - changes reference Standard
2025-12-06 fix(api): corrigir serializacao de datas no InstrumentApiResource
2025-12-06 feat - changes instrumentapi
2025-12-06 fix(api): ajustar filtros de busca por numero de serie na API de instrumentos
2025-12-06 feat - changes
2025-12-06 refactor(metrologia): sincronizar relacionamentos de itens de checklist e padroes de referencia
2025-12-06 style(metrologia): padronizar icones e colunas nas tabelas de calibracao e checklists
2025-12-06 feat(metrologia): aprimorar gerenciador de relacionamentos de calibracoes no Filament
2025-12-09 feat - melhoras padrões de referencia
2025-12-09 feat(metrologia): expandir formularios de tipos de instrumentos e padroes de referencia
2026-01-08 refactor(metrologia): implementar acoes para emissao de certificados e criacao de checklists
2026-01-08 mudancas - teste antigravity
2026-01-09 refactor(metrologia): consolidar acoes de processamento de calibracao e calculo metrologico
2026-01-09 mudancas - teste antigravity 2
2026-05-29 feat(iot): fix mqtt bridge parsing and optimize telemetry processing
2026-05-29 fix(iot): corrigir parsing da ponte MQTT e otimizar processamento de telemetria
2026-05-29 feat(metrologia): completar modulo de metrologia com calibracoes, nao conformidades e materiais
2026-05-29 feat(metrology): complete metrology module with calibration, NC and materials
2026-05-29 refactor: implement multi-tenancy core and restructure project into modules
2026-05-29 refactor(core): implementar multi-tenancy central e reestruturar projeto em modulos
2026-05-29 chore(repo): limpar arquivos desnecessarios de debug e documentacao temporaria
2026-05-29 chore: cleanup unnecessary debug and documentation files
